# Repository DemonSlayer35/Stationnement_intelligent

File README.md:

# Stationnement intelligent
Projet de fin de DEC en TSO (Etienne Dubé et Mohammad Barin Wahidi)

## Pour démarrer le projet, il faut d'abord suivre les étapes d'installation des fichiers Installation.md 
(Stationnement_intelligent/Installation.md et Stationnement_intelligent/code_esp/Installation.md)
https://github.com/DemonSlayer35/Stationnement_intelligent/blob/main/Installation.md et
https://github.com/DemonSlayer35/Stationnement_intelligent/blob/main/code_esp/Installation.md

## Ensuite, il faut suivre les étapes d'opération des fichiers Procedure.md
(Stationnement_intelligent/page_web/Procedure.md et Stationnement_intelligent/code_esp/Procedure.md)
https://github.com/DemonSlayer35/Stationnement_intelligent/blob/main/page_web/Procedure.md et https://github.com/DemonSlayer35/Stationnement_intelligent/blob/main/code_esp/Procedure.md

## Installation.md 
* Ce fichier contient les procédures d'installation de la suite Yolov5 et les étapes pour l'entraînement de l'IA ainsi que la détection d'objets.

## KiCad
* Ce dossier contient le projet KiCad (schéma électrique, PCB et fichiers de fabrication) de l'ESP32 pour la barrière de stationnement.

## code 
* Ce dossier contient les scripts en Python pour la détection des images avec la caméra et l'affichage du stationnement sur un écran.
* Le code envoie les résultats de la détection d'emplacements libres par MQTT au broker pour la construction de la page Web du stationnement.

## code_esp
* Ce dossier contient le code (code_esp.ino) à téléverser dans l'ESP, ainsi que les fichiers (dans le dossier /data) à téléverser dans le système de fichiers de l'ESP32. 
* Le code de l'ESP génère un point d'accès qui sert la page Web du stationnement intelligent via un portail captif.

## data_parking 
* Ce dossier contient les images de stationnement pour l'entraînement de l'IA et les étiquettes correspondantes (vide, plein, logo).
* Sont aussi inclus les modèles résultants de l'entraînement qui permettent de détecter les étiquettes voulues.

## page_web
* Ce dossier contient les fichiers de code pour la génération de la page Web affichant les places de stationnement.

## stl
* Ce dossier contient les fichiers 3D de la barrière.

## schema.drawio
* Ce fichier est un schéma bloc du fonctionnement du projet de stationnement intelligent (à ouvrir avec draw.io)

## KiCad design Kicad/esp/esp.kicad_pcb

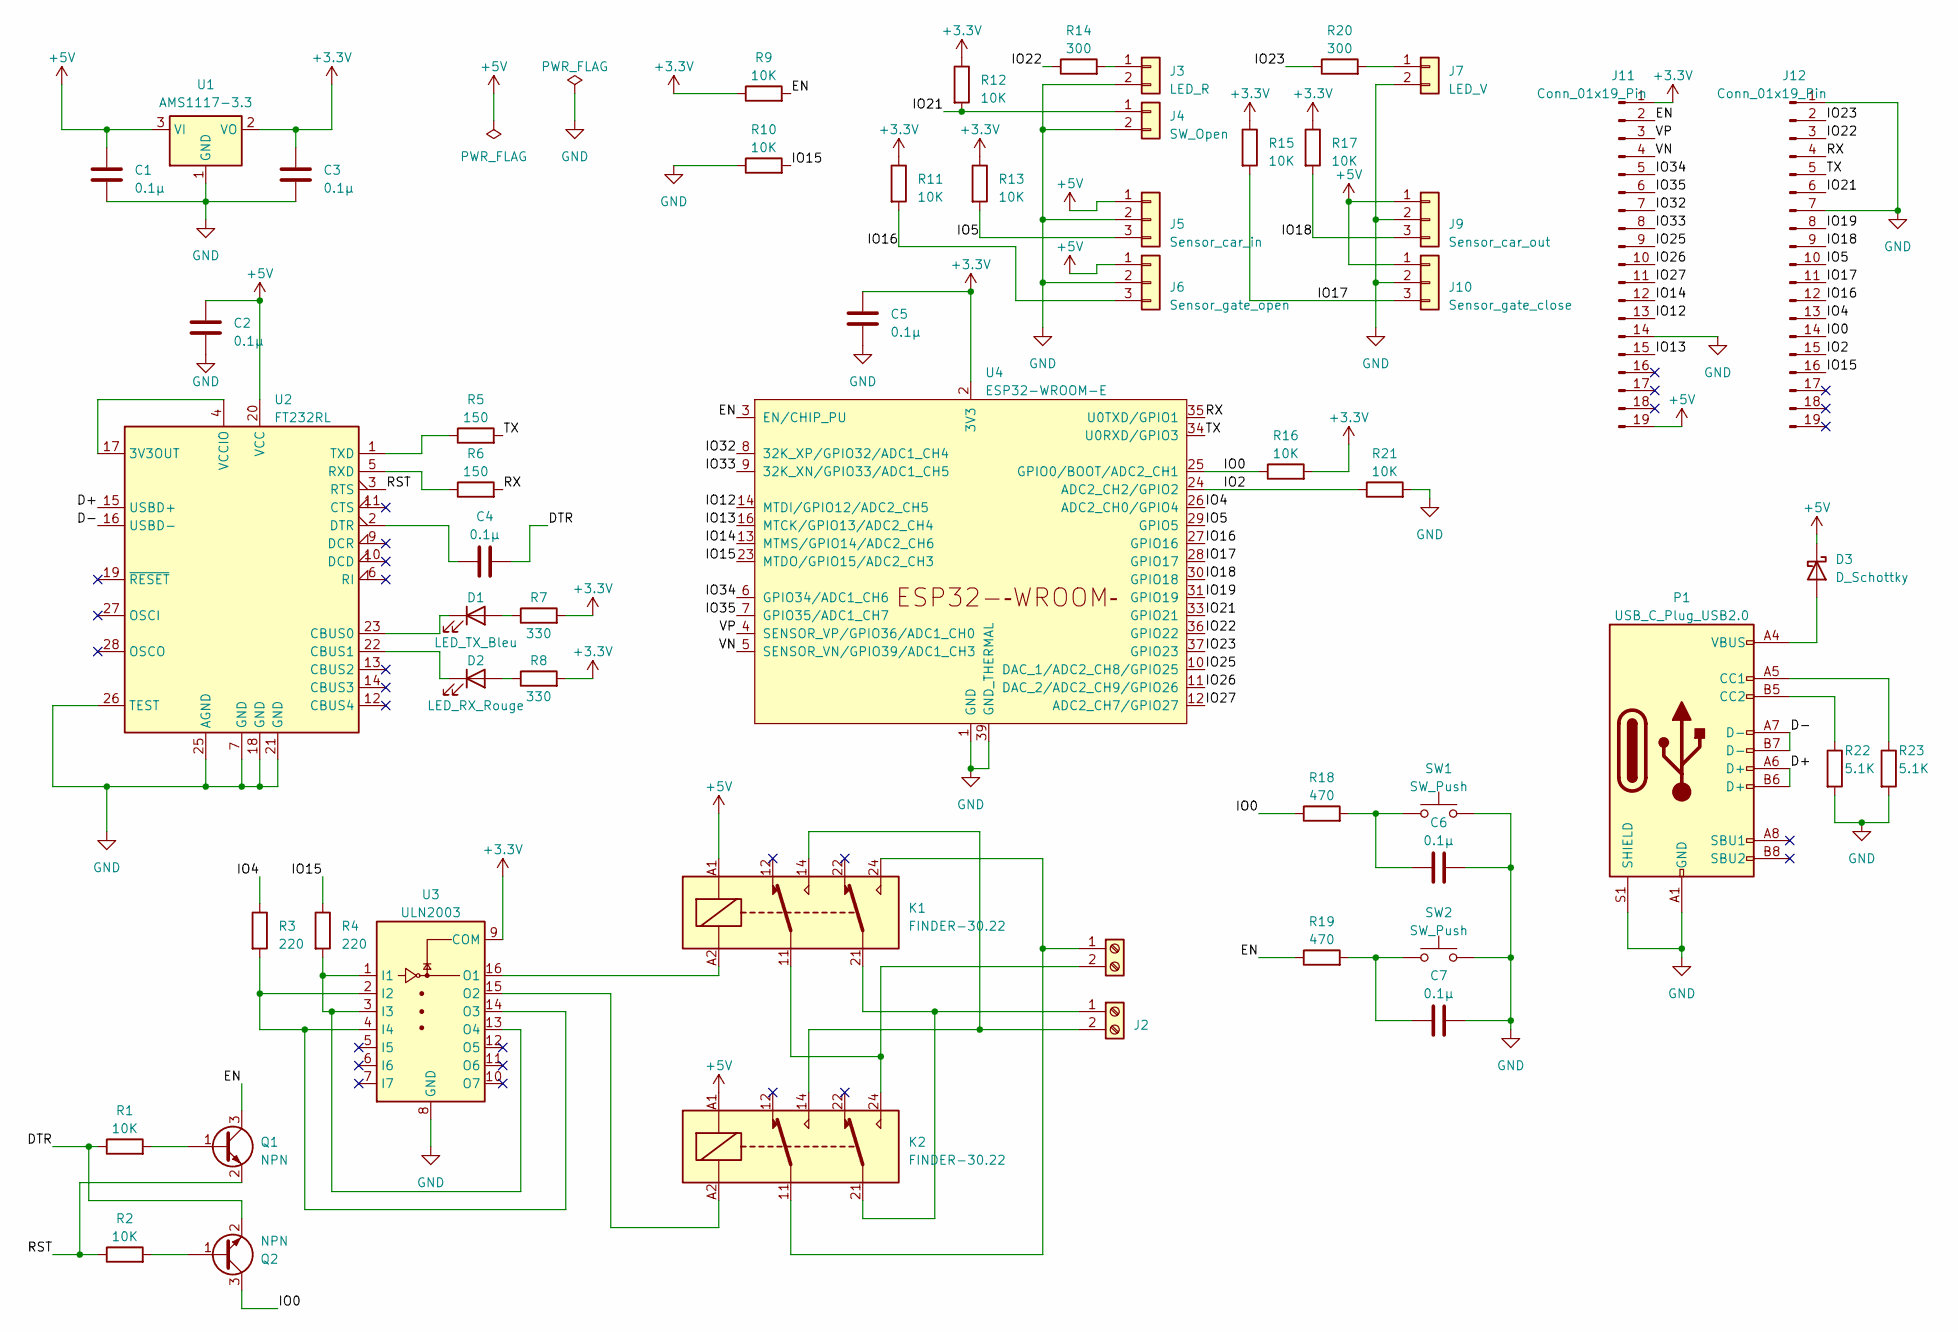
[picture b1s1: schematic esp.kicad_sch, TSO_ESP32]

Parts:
C1, C2, C3, C4, C5, C6, C7: 0.1µ; C_0805_2012Metric_Pad1.18x1.45mm_HandSolder
D1: LED_TX_Bleu; LED_0805_2012Metric_Pad1.15x1.40mm_HandSolder
D2: LED_RX_Rouge; LED_0805_2012Metric_Pad1.15x1.40mm_HandSolder
D3: D_Schottky; D_0805_2012Metric_Pad1.15x1.40mm_HandSolder
J1, J2: TerminalBlock_bornier-2_P5.08mm
J3: LED_R; PinHeader_1x02_P2.54mm_Vertical
J4: SW_Open; PinHeader_1x02_P2.54mm_Vertical
J5: Sensor_car_in; PinHeader_1x03_P2.54mm_Vertical
J6: Sensor_gate_open; PinHeader_1x03_P2.54mm_Vertical
J7: LED_V; PinHeader_1x02_P2.54mm_Vertical
J9: Sensor_car_out; PinHeader_1x03_P2.54mm_Vertical
J10: Sensor_gate_close; PinHeader_1x03_P2.54mm_Vertical
J11, J12: Conn_01x19_Pin; PinHeader_1x19_P2.54mm_Vertical
K1, K2: FINDER-30.22; Relay_DPDT_Finder_30.22
P1: USB_C_Plug_USB2.0; USB_C_Receptacle_GCT_USB4105-xx-A_16P_TopMnt_Horizontal
Q1, Q2: NPN; SOT-23
R1, R2, R9, R10, R11, R12, R13, R15, R16, R17, R21: 10K; R_0805_2012Metric_Pad1.20x1.40mm_HandSolder
R3, R4: 220; R_0805_2012Metric_Pad1.20x1.40mm_HandSolder
R5, R6: 150; R_0805_2012Metric_Pad1.20x1.40mm_HandSolder
R7, R8: 330; R_0805_2012Metric_Pad1.20x1.40mm_HandSolder
R14, R20: 300; R_0805_2012Metric_Pad1.20x1.40mm_HandSolder
R18, R19: 470; R_0805_2012Metric_Pad1.20x1.40mm_HandSolder
R22, R23: 5.1K; R_0805_2012Metric_Pad1.20x1.40mm_HandSolder
SW1, SW2: SW_Push; SW_SPST_CK_RS282G05A3
U1: AMS1117-3.3; SOT-223-3_TabPin2
U2: FT232RL; SSOP-28_5.3x10.2mm_P0.65mm
U3: ULN2003; SO-16_3.9x9.9mm_P1.27mm
U4: ESP32-WROOM-E; ESP32-WROOM-32E

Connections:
+3.3V: C3.1, C5.1, J11.1, R7.2, R8.2, R9.1, R11.1, R12.1, R13.1, R15.1, R16.2, R17.1, U1.2 (VO), U3.9 (COM), U4.2 (3V3)
+5V: C1.1, C2.1, D3.1 (K), J5.1, J6.1, J9.1, J10.1, J11.19, K1.A1, K2.A1, U1.3 (VI), U2.20 (VCC)
/D+: P1.A6 (D+), P1.B6 (D+), U2.15 (USBD+)
/D-: P1.A7 (D-), P1.B7 (D-), U2.16 (USBD-)
/DTR: C4.2, Q2.2 (E), R1.1
/EN: J11.2, Q1.3 (C), R9.2, R19.1, U4.3 (EN/CHIP_PU)
/IO0: J12.14, Q2.3 (C), R16.1, R18.1, U4.25 (GPIO0/BOOT/ADC2_CH1)
/IO2: J12.15, R21.1, U4.24 (ADC2_CH2/GPIO2)
/IO4: J12.13, R3.1, U4.26 (ADC2_CH0/GPIO4)
/IO5: J5.3, J12.10, R13.2, U4.29 (GPIO5)
/IO12: J11.13, U4.14 (MTDI/GPIO12/ADC2_CH5)
/IO13: J11.15, U4.16 (MTCK/GPIO13/ADC2_CH4)
/IO14: J11.12, U4.13 (MTMS/GPIO14/ADC2_CH6)
/IO15: J12.16, R4.1, R10.2, U4.23 (MTDO/GPIO15/ADC2_CH3)
/IO16: J6.3, J12.12, R11.2, U4.27 (GPIO16)
/IO17: J10.3, J12.11, R15.2, U4.28 (GPIO17)
/IO18: J9.3, J12.9, R17.2, U4.30 (GPIO18)
/IO19: J12.8, U4.31 (GPIO19)
/IO21: J4.1, J12.6, R12.2, U4.33 (GPIO21)
/IO22: J12.3, R14.1, U4.36 (GPIO22)
/IO23: J12.2, R20.1, U4.37 (GPIO23)
/IO25: J11.9, U4.10 (DAC_1/ADC2_CH8/GPIO25)
/IO26: J11.10, U4.11 (DAC_2/ADC2_CH9/GPIO26)
/IO27: J11.11, U4.12 (ADC2_CH7/GPIO27)
/IO32: J11.7, U4.8 (32K_XP/GPIO32/ADC1_CH4)
/IO33: J11.8, U4.9 (32K_XN/GPIO33/ADC1_CH5)
/IO34: J11.5, U4.6 (GPIO34/ADC1_CH6)
/IO35: J11.6, U4.7 (GPIO35/ADC1_CH7)
/RST: Q1.2 (E), R2.1, U2.3 (RTS)
/RX: J12.4, R6.2, U4.35 (U0TXD/GPIO1)
/TX: J12.5, R5.2, U4.34 (U0RXD/GPIO3)
/VN: J11.4, U4.5 (SENSOR_VN/GPIO39/ADC1_CH3)
/VP: J11.3, U4.4 (SENSOR_VP/GPIO36/ADC1_CH0)
GND: C1.2, C2.2, C3.2, C5.2, C6.2, C7.2, J3.2, J4.2, J5.2, J6.2, J7.2, J9.2, J10.2, J11.14, J12.1, J12.7, P1.A1 (GND), P1.A12 (GND), P1.B1 (GND), P1.B12 (GND), P1.S1 (SHIELD), R10.1, R21.2, R22.2, R23.2, SW1.2, SW2.2, U1.1 (GND), U2.7 (GND), U2.18 (GND), U2.21 (GND), U2.25 (AGND), U2.26 (TEST), U3.8 (GND), U4.1 (GND), U4.15 (GND), U4.38 (GND), U4.39 (GND_THERMAL)
unnamed: C6.1, R18.2, SW1.1
unnamed: C7.1, R19.2, SW2.1
unnamed: D1.2 (A), R7.1
unnamed: D1.1 (K), U2.23 (CBUS0)
unnamed: D2.2 (A), R8.1
unnamed: D2.1 (K), U2.22 (CBUS1)
unnamed: D3.2 (A), P1.A4 (VBUS), P1.A9 (VBUS), P1.B4 (VBUS), P1.B9 (VBUS)
unnamed: J1.1, K1.24, K2.11
unnamed: J1.2, K1.11, K2.24
unnamed: J2.1, K1.21, K2.21
unnamed: J2.2, K1.14, K2.14
unnamed: J3.1, R14.2
unnamed: J7.1, R20.2
unnamed: P1.A5 (CC1), R23.1
unnamed: P1.B5 (CC2), R22.1
unnamed: Q1.1 (B), R1.2
unnamed: Q2.1 (B), R2.2
unnamed: U2.4 (VCCIO), U2.17 (3V3OUT)
unnamed: C4.1, U2.2 (DTR)
unnamed: R6.1, U2.5 (RXD)
unnamed: R5.1, U2.1 (TXD)
unnamed: R4.2, U3.1 (I1), U3.3 (I3), U3.13 (O4)
unnamed: R3.2, U3.2 (I2), U3.4 (I4), U3.14 (O3)
unnamed: K1.A2, U3.16 (O1)
unnamed: K2.A2, U3.15 (O2)

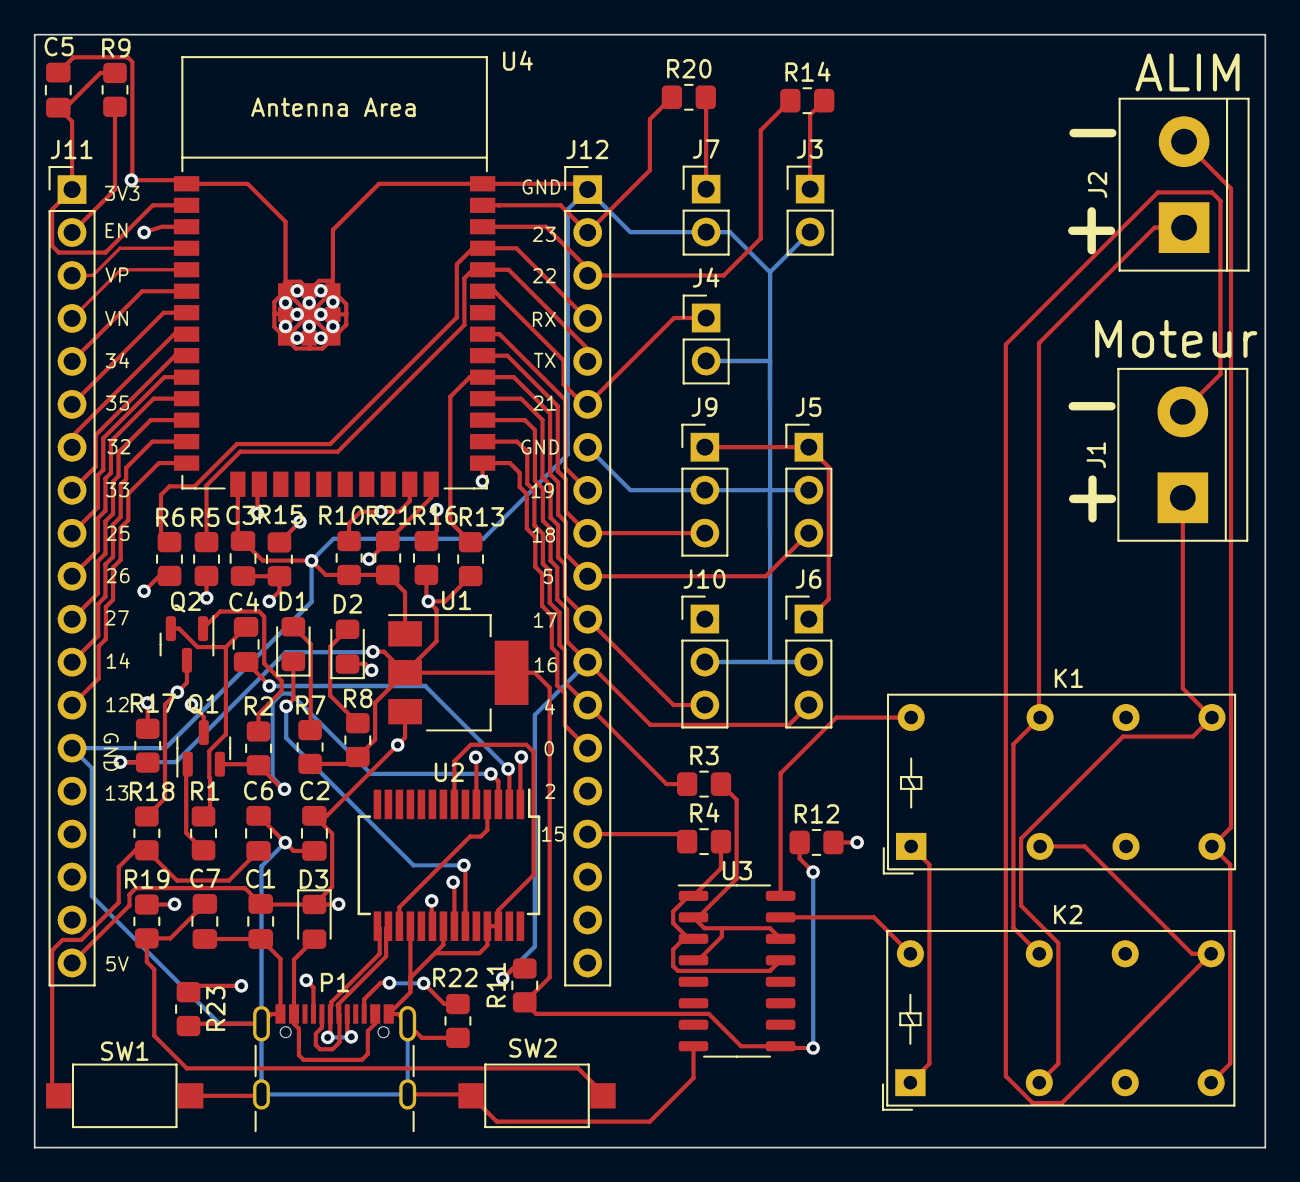
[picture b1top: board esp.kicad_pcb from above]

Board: 4 copper layers, 72.7 x 65.8 mm, 55 parts (0 on the bottom side), 59 nets.

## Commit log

2023-01-19 Ajout des codes Arduino et du schéma électrique KiCad
2023-01-23 Ajout d'un classeur Excel avec les prix du projet pour les TA
2023-01-24 Ajout d'un programme LabView qui identifie un appareil par son IP
2023-01-24 Update README.md
    Etienne ça ne prend pas d'accent aigu.
2023-01-24 Changement de projet/Suppression des anciens fichiers
2023-01-31 Ajout du squelette pour le dataset
2023-01-31 Ajout d'autres images
2023-01-31 Ajout labels
2023-02-02 Photos
2023-02-02 Photo manquante
2023-02-02 Mes 6s
2023-02-02 Mes 6 derniers
2023-02-02 name changed
2023-02-02 Training Satisfaisant
2023-02-06 Ajout de la procédure d'installation de YOLOv5
2023-02-06 Ajout de la méthode pour créer un dataset
2023-02-06 Ajout de la méthode d'entraînement de l'IA
2023-02-06 Projet.py : Récupération des données de détection du best.py
2023-02-06 Ajout des étapes de validation de l'entraînement
2023-02-07 Nouvelle images
2023-02-07 Nouvelle images label
2023-02-07 mes 12 images
2023-02-07 une image mal étiquettée
2023-02-07 More pictures
2023-02-07 mes 9 images
2023-02-07 More labaling
2023-02-07 Changement de label plein à car
2023-02-07 enlever plein de classes.txt
2023-02-07 Correction label
2023-02-07 Projet.py frame avec rectangle
2023-02-09 New .pt
2023-02-09 Create Installation.md
    Déplacement de la procédure d'installation du README.md à Installation.md
2023-02-09 Training with yolov5m.pt and replace label on some images
2023-02-09 Code détection amélioré avec moyenne ChatGPT
2023-02-13 Ajout du code pour l'écran de stationnement
2023-02-13 Création d'un dossier pour le code
2023-02-13 Modification des codes camera et ecran qui sont maintenant compatibles entre eux
2023-02-15 Ajout d'un dossier page_web pour la page web
2023-02-16 camera.py - trie des coordonées (pas fonctionnelle)
2023-02-17 Ajout d'un code pour publier en mqtt la liste des places
2023-02-20 Classement fonctionnelle
2023-03-06 Code inutile efface
2023-03-07 Tentatice de mofification de camera.py piur cree une class
2023-03-13 Kicad
2023-03-16 Shemat esp
2023-03-28 Ajout du code de l'ESP pour la page web par point d'accès
2023-03-28 Kicad Final
2023-04-04 Schema Bloc
2023-04-11 Class termine
2023-04-11 Code de l'ESP commenté
2023-04-11 Code js de la page Web commenté
2023-04-11 Code js de l'ESP commenté
2023-04-13 Schema
2023-04-13 Commentaire
2023-04-24 MAJ Schema
2023-04-25 Ébauche du code pour la barrière
2023-05-02 Ajout du code de la barriere
2023-05-08 Code ESP complet
2023-05-15 Ajout des fichiers 3D (stl) de la barrière
2023-05-15 Retrait de test_barriere
2023-05-15 En-tête du code de l'ESP
